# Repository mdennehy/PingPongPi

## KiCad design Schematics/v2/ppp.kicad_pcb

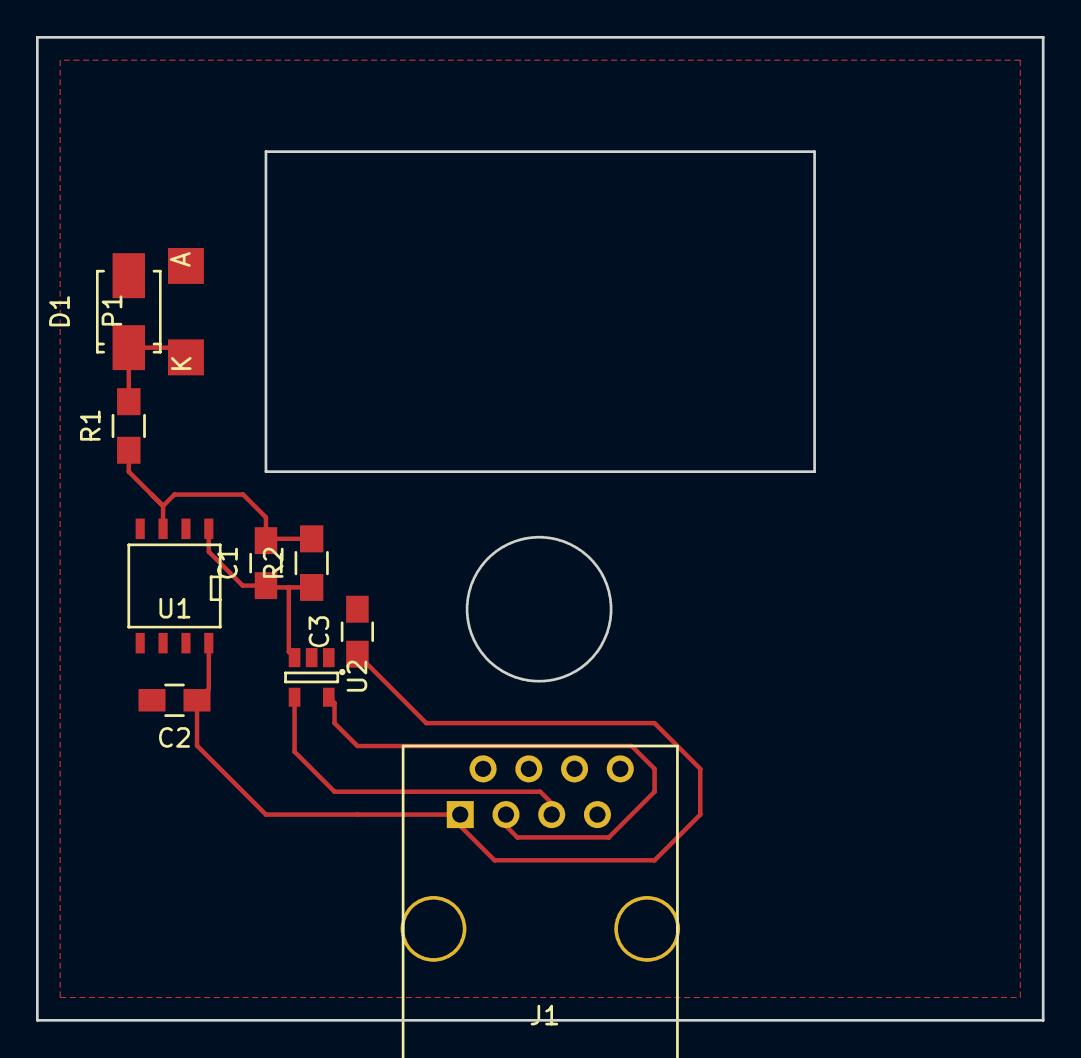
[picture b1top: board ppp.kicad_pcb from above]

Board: 2 copper layers, 55.9 x 54.6 mm, 10 parts (0 on the bottom side), 7 nets.

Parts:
C1, C2, C3: C; C_0805_HandSoldering
D1: ZENER 2v7; SMA_Standard
J1: RJ45; RJ45_8
P1: LDT; NetTie-I_SMD
R1, R2: R; R_0805_HandSoldering
U1: TL082; SOIC-8-N
U2: MCP3221; SOT-23-5

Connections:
+3V3: C2.1, C3.1, J1.1, U1.8, U2.1
GND: C2.2, C3.2, D1.2, J1.2, J1.4, J1.6, J1.8, P1.1, U1.2, U1.4, U2.2
unnamed: C1.1, R2.1, U1.1, U2.3
unnamed: C1.2, R1.1, R2.2, U1.3
unnamed: D1.1, P1.2, R1.2
unnamed: J1.3, U2.5
unnamed: J1.5, U2.4

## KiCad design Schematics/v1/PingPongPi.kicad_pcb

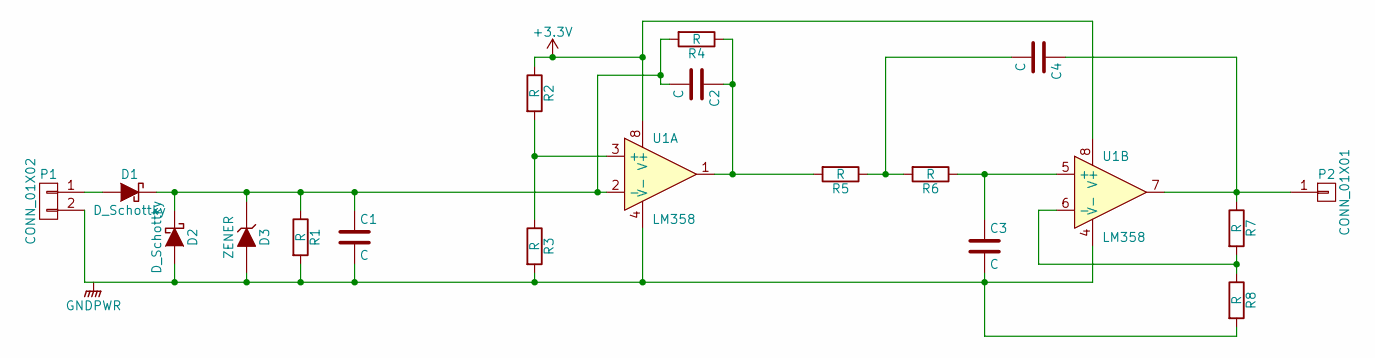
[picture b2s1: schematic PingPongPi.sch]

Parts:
C1, C2, C3, C4: C; C_Disc_D3_P2.5
D1, D2: D_Schottky; Diode_DO-35_SOD27_Horizontal_RM10
D3: ZENER; Diode_DO-35_SOD27_Horizontal_RM10
P1: CONN_01X02; Socket_Strip_Straight_1x02
P2: CONN_01X01; Socket_Strip_Straight_1x01
R1, R2, R3, R4, R5, R6, R7, R8: R; Resistor_Horizontal_RM10mm
U1: LM358; DIP-8_W7.62mm

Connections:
+3V3: R2.1, U1.8 (V+)
unnamed: C1.1, C2.2, D1.1 (K), D2.1 (K), D3.1 (K), R1.1, R4.2, U1.2 (-)
unnamed: C1.2, C3.2, D2.2 (A), D3.2 (A), P1.2, R1.2, R3.2, R8.2, U1.4 (V-)
unnamed: C2.1, R4.1, R5.2, U1.1
unnamed: C3.1, R6.1, U1.5 (+)
unnamed: C4.1, P2.1, R7.1, U1.7
unnamed: C4.2, R5.1, R6.2
unnamed: D1.2 (A), P1.1
unnamed: R2.2, R3.1, U1.3 (+)
unnamed: R7.2, R8.1, U1.6 (-)

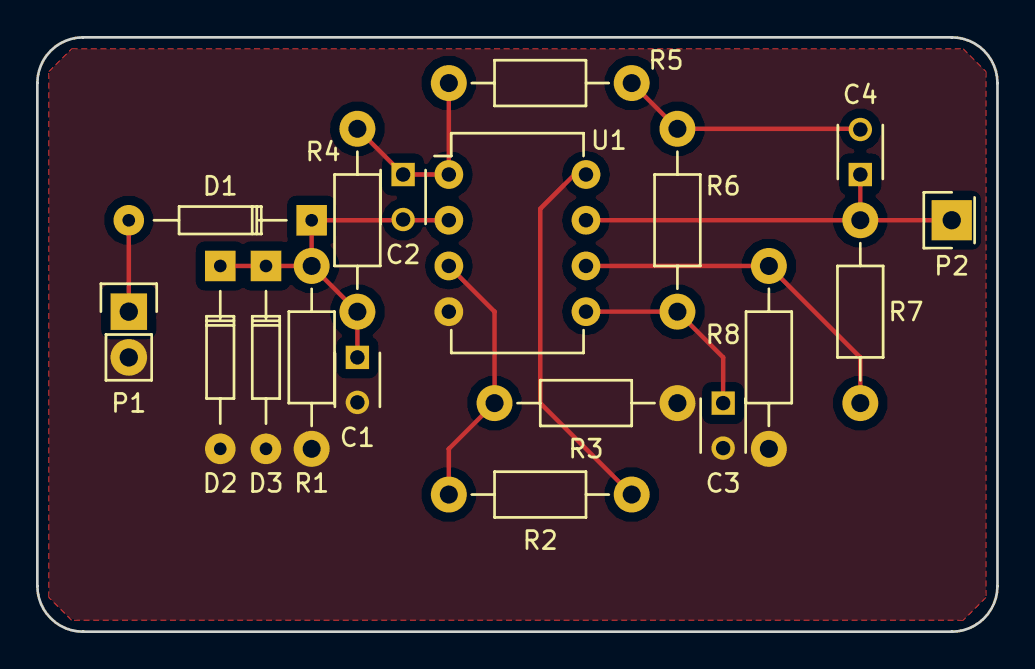
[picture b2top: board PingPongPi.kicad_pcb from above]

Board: 2 copper layers, 53.3 x 33.0 mm, 18 parts (0 on the bottom side), 10 nets.

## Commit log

2016-02-14 Initial commit.
2016-02-15 Tweaking erlang. Just mucking about.
